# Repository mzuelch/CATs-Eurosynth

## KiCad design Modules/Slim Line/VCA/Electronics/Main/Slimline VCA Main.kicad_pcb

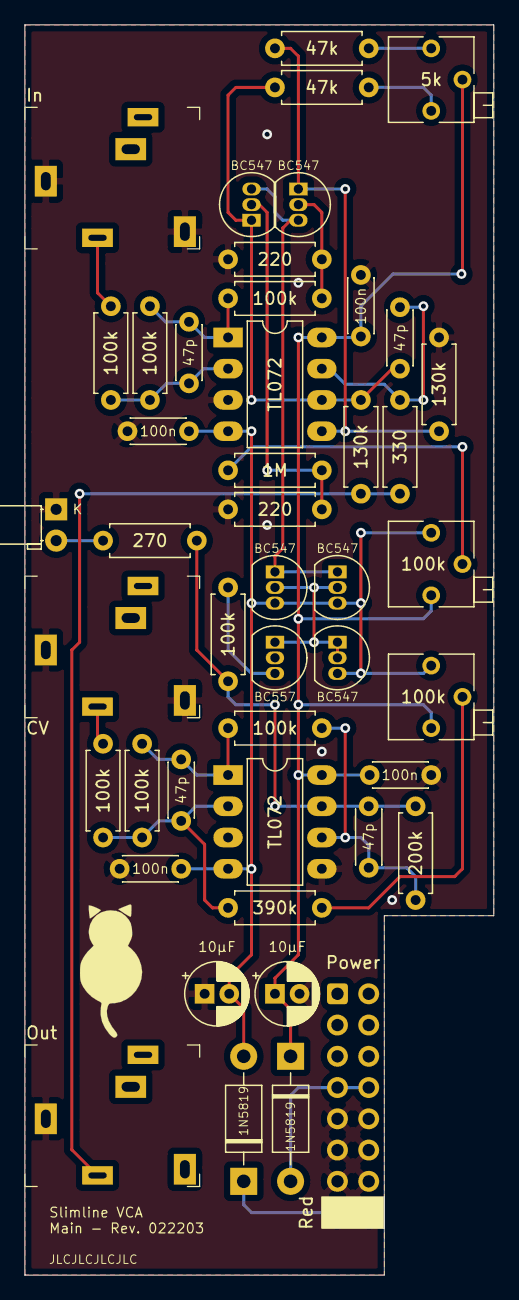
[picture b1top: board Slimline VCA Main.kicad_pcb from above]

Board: 2 copper layers, 38.1 x 101.6 mm, 46 parts (0 on the bottom side), 27 nets.

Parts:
C1, C2, C3, C4: 47p; C_Disc_D4.3mm_W1.9mm_P5.00mm
C5, C6: 10µF; CP_Radial_D5.0mm_P2.00mm
C7, C8, C9, C10: 100n; C_Disc_D4.3mm_W1.9mm_P5.00mm
D1, D2: 1N5819; D_DO-41_SOD81_P10.16mm_Horizontal
D3: LED; LED_D3.0mm_Horizontal_O1.27mm_Z2.0mm
J1: CV; Jack_3.5mm_QingPu_WQP-PJ324M
J2: In; Jack_3.5mm_QingPu_WQP-PJ324M
J3: Out; Jack_3.5mm_QingPu_WQP-PJ324M
J4: Power; Power_2x8_Horizontal
Q1: BC557; TO-92_Inline
Q2, Q3, Q4, Q5, Q6: BC547; TO-92_Inline
R1: 390k; R_Axial_DIN0207_L6.3mm_D2.5mm_P7.62mm_Horizontal
R2, R3, R4, R6, R7, R8, R9: 100k; R_Axial_DIN0207_L6.3mm_D2.5mm_P7.62mm_Horizontal
R5: 200k; R_Axial_DIN0207_L6.3mm_D2.5mm_P7.62mm_Horizontal
R10, R13: 220; R_Axial_DIN0207_L6.3mm_D2.5mm_P7.62mm_Horizontal
R11, R12: 47k; R_Axial_DIN0207_L6.3mm_D2.5mm_P7.62mm_Horizontal
R14: 1M; R_Axial_DIN0207_L6.3mm_D2.5mm_P7.62mm_Horizontal
R15, R16: 130k; R_Axial_DIN0207_L6.3mm_D2.5mm_P7.62mm_Horizontal
R17: 330; R_Axial_DIN0207_L6.3mm_D2.5mm_P7.62mm_Horizontal
R18: 270; R_Axial_DIN0207_L6.3mm_D2.5mm_P7.62mm_Horizontal
RV1, RV3: 100k; Potentiometer_Bourns_3266P_Horizontal
RV2: 5k; Potentiometer_Bourns_3266P_Horizontal
U1, U2: TL072; DIP-8_W7.62mm_LongPads

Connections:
+12V: C5.1, C7.2, C9.2, D1.1, RV1.1, RV2.2, RV3.1, U1.8, U2.8
-12V: C6.2, C8.1, C10.1, D2.2, Q2.3, Q4.3, Q5.3, RV1.3, RV3.3, U1.4, U2.4
GND: C5.2, C6.1, C7.1, C8.2, C9.1, C10.2, D3.1, J1.S, J1.TN, J2.S, J2.TN, J3.S, J4.GND, Q1.2, R10.2, R13.2, R15.2, U1.3, U2.3, U2.5
unnamed: C1.1, R3.1, R4.2, U2.1
unnamed: C1.2, R1.1, R2.1, R3.2, U2.2
unnamed: C2.1, R5.1, R6.2, R18.2, U2.7
unnamed: C2.2, R4.1, R5.2, U2.6
unnamed: C3.1, R8.1, R9.2, U1.1
unnamed: C3.2, R7.1, R8.2, U1.2
unnamed: C4.1, R17.2, U1.7
unnamed: C4.2, Q6.1, R12.2, R16.2, U1.6
unnamed: D1.2, J4.+12V
unnamed: D2.1, J4.-12V
unnamed: D3.2, R18.1
unnamed: J1.T, R2.2
unnamed: J2.T, R7.2
unnamed: J3.T, R16.1, R17.1
unnamed: Q1.1, Q2.1, Q2.2, Q4.2, Q5.2
unnamed: Q1.3, R6.1
unnamed: Q3.1, R11.2, R15.1, U1.5
unnamed: Q3.2, R9.1, R10.1
unnamed: Q3.3, Q4.1, Q5.1, Q6.3
unnamed: Q6.2, R13.1, R14.2
unnamed: R1.2, RV1.2
unnamed: R11.1, RV2.3
unnamed: R12.1, RV2.1
unnamed: R14.1, RV3.2

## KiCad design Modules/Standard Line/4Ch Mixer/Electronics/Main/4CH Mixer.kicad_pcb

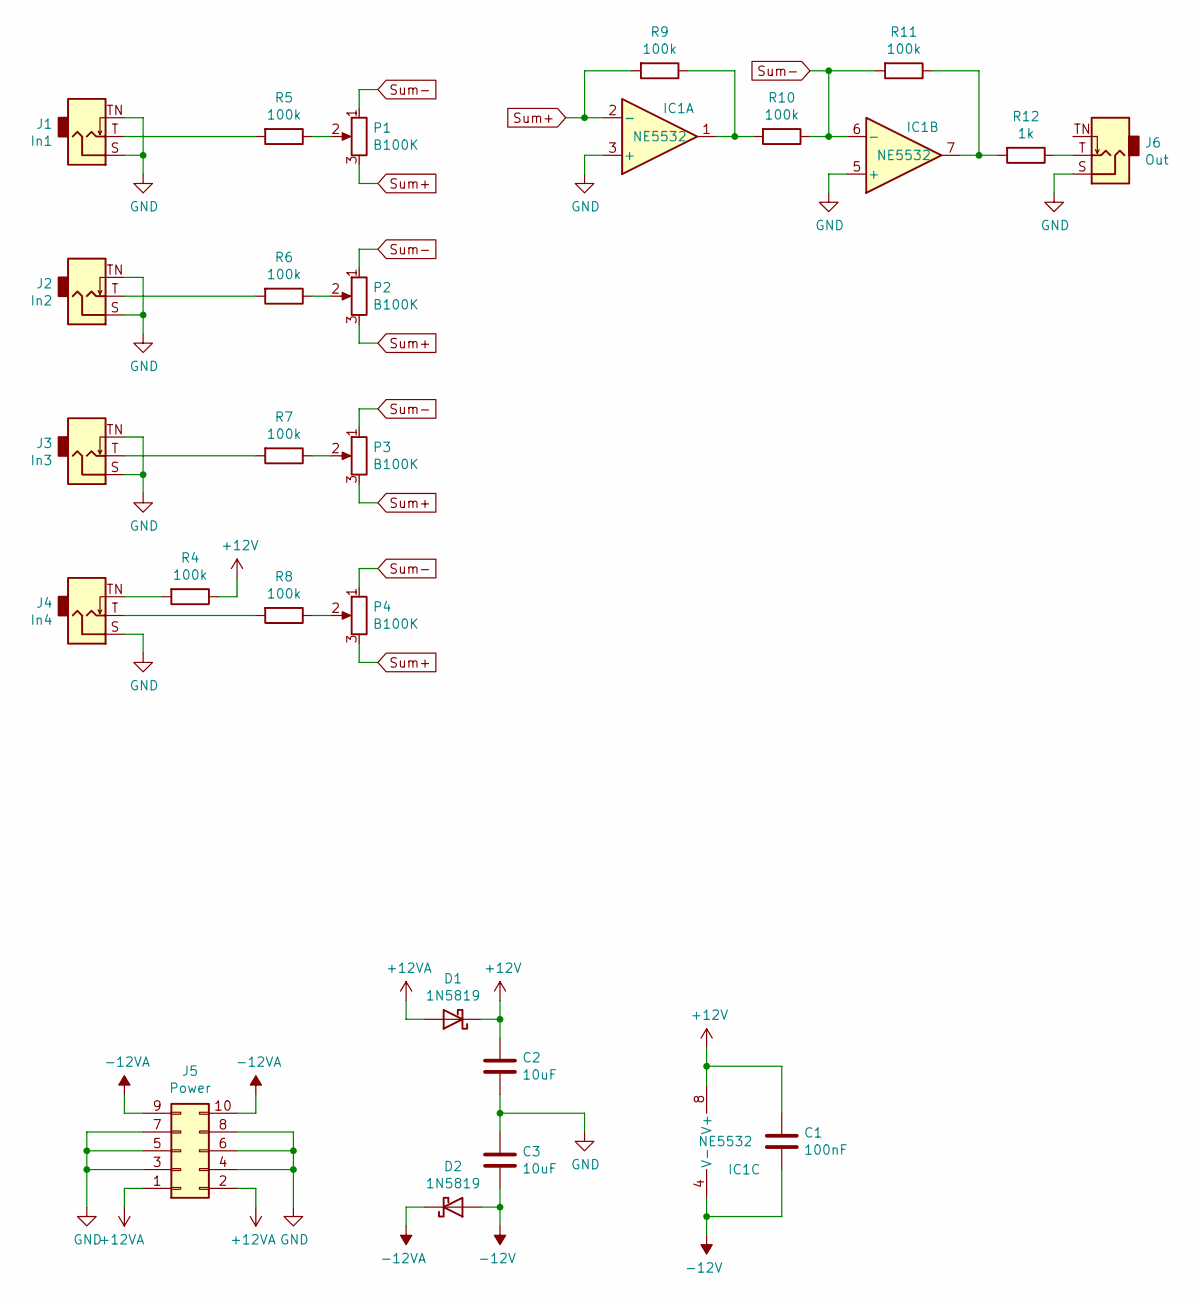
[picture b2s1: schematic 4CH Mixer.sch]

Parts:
C1: 100nF; C_0805_2012Metric; LCSC C49678
C2, C3: 10uF; C_0805_2012Metric; LCSC C15850
D1, D2: 1N5819; D_SOD-123; LCSC C8598
IC1: NE5532; SOIC-8_3.9x4.9mm_P1.27mm; LCSC C7426
J1: In1; PJ-301-M-12
J2: In2; PJ-301-M-12
J3: In3; PJ-301-M-12
J4: In4; PJ-301-M-12
J5: Power; PinHeader_2x05_P2.54mm_Vertical
J6: Out; PJ-301-M-12
P1, P2, P3, P4: B100K; Potentiometer_Alpha_RD901F-40-00D_Single_Vertical
R4, R5, R6, R7, R8, R9, R10, R11: 100k; R_0805_2012Metric; LCSC C17407
R12: 1k; R_0805_2012Metric; LCSC C17513

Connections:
+12V: C1.1, C2.1, D1.1 (K), IC1.8 (V+), R4.1
+12VA: D1.2 (A), J5.1, J5.2
-12V: C1.2, C3.2, D2.2 (A), IC1.4 (V-)
-12VA: D2.1 (K), J5.9, J5.10
GND: C2.2, C3.1, IC1.3 (+), IC1.5 (+), J1.S, J1.TN, J2.S, J2.TN, J3.S, J3.TN, J4.S, J5.3, J5.4, J5.5, J5.6, J5.7, J5.8, J6.S
unnamed: IC1.1, R9.1, R10.2
unnamed: IC1.7, R11.1, R12.2
unnamed: J1.T, R5.2
unnamed: J2.T, R6.2
unnamed: J3.T, R7.2
unnamed: J4.T, R8.2
unnamed: J4.TN, R4.2
unnamed: J6.T, R12.1
unnamed: P1.2, R5.1
unnamed: P2.2, R6.1
unnamed: P3.2, R7.1
unnamed: P4.2, R8.1
Sum+: IC1.2 (-), P1.3, P2.3, P3.3, P4.3, R9.2
Sum-: IC1.6 (-), P1.1, P2.1, P3.1, P4.1, R10.1, R11.2

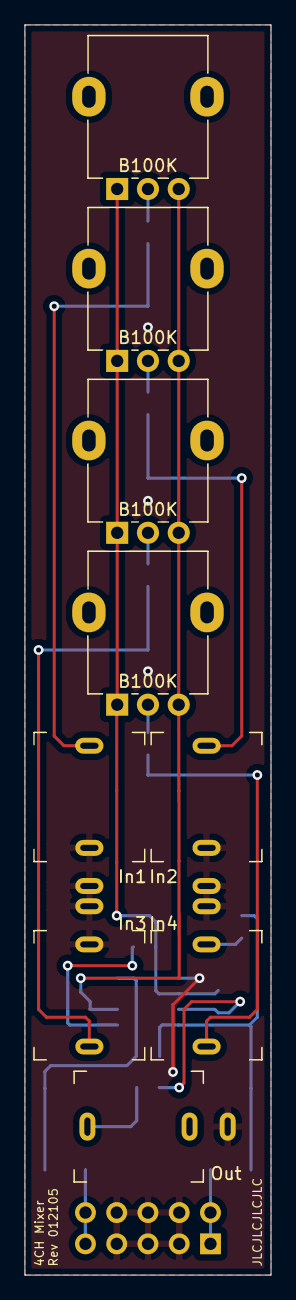
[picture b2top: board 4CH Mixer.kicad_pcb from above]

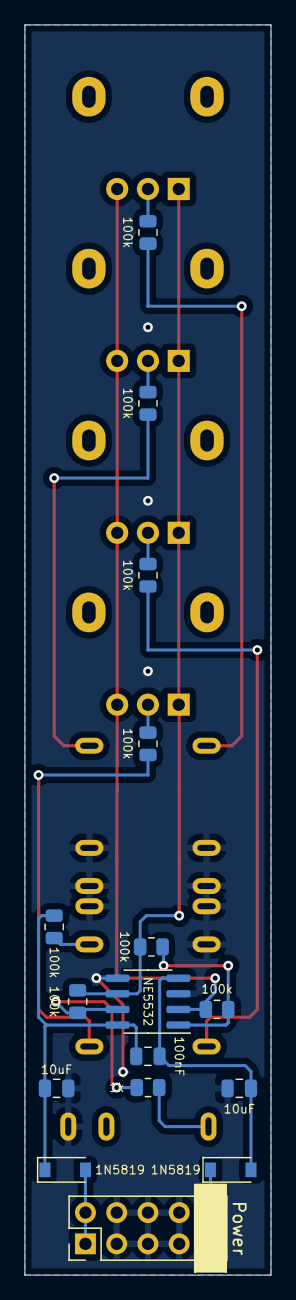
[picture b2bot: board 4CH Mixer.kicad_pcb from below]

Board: 2 copper layers, 20.0 x 101.6 mm, 25 parts (16 on the bottom side), 19 nets.

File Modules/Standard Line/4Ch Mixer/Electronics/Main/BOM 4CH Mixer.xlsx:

Comment | Designator | Footprint | LCSC
1N5819 | D2,D1 | D_SOD-123 | C8598
10uF | C3,C2 | C_0805_2012Metric | C15850
Out | J6 | PJ-301-M-12
In4 | J4 | PJ-301-M-12
In3 | J3 | PJ-301-M-12
In2 | J2 | PJ-301-M-12
In1 | J1 | PJ-301-M-12
NE5532 | IC1 | SOIC-8_3.9x4.9mm_P1.27mm | C7426
1k | R12 | R_0805_2012Metric | C17513
100k | R11,R10,R9,R8,R7,R6,R5,R4 | R_0805_2012Metric | C17407
B100K | P4,P3,P2,P1 | Potentiometer_Alpha_RD901F-40-00D_Single_Vertical
Power | J5 | PinHeader_2x05_P2.54mm_Vertical
100nF | C1 | C_0805_2012Metric | C49678

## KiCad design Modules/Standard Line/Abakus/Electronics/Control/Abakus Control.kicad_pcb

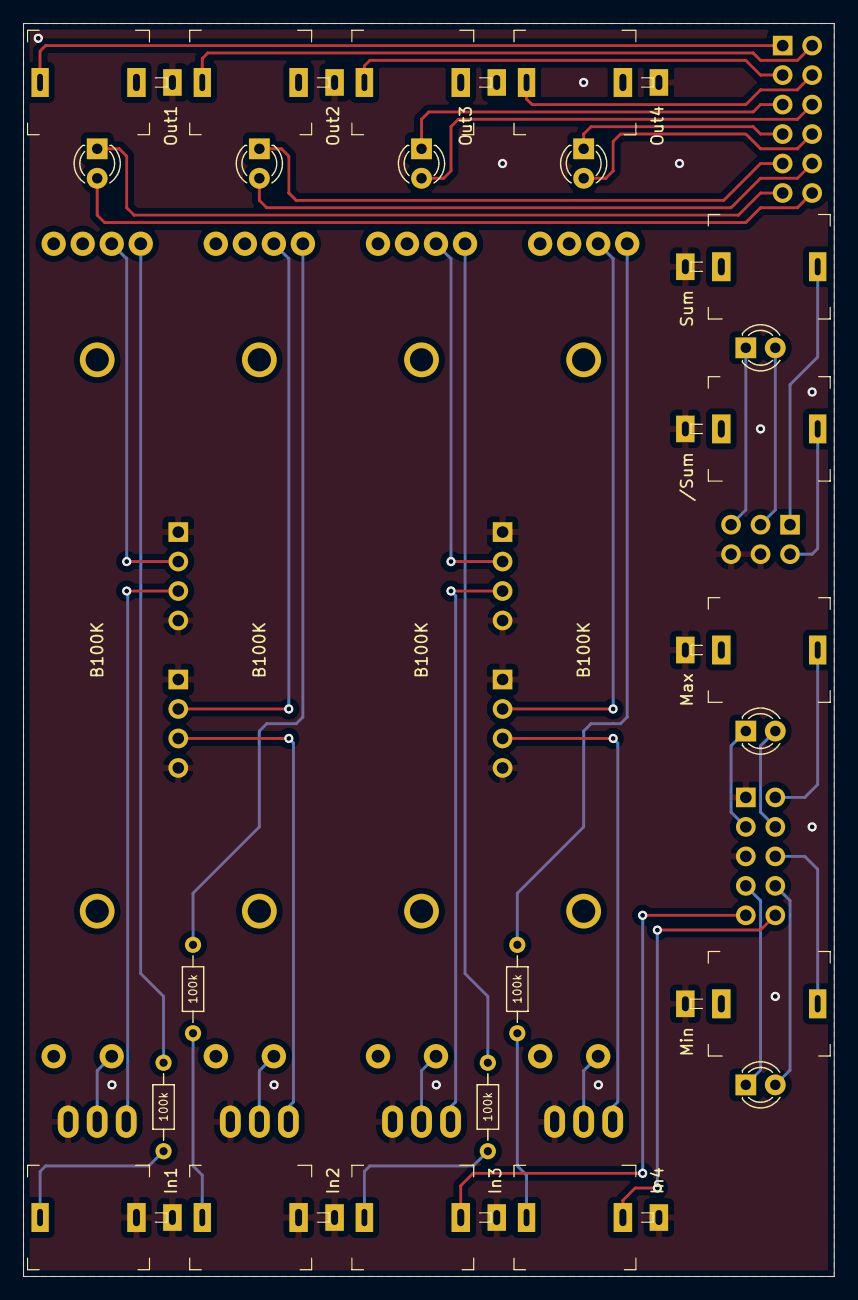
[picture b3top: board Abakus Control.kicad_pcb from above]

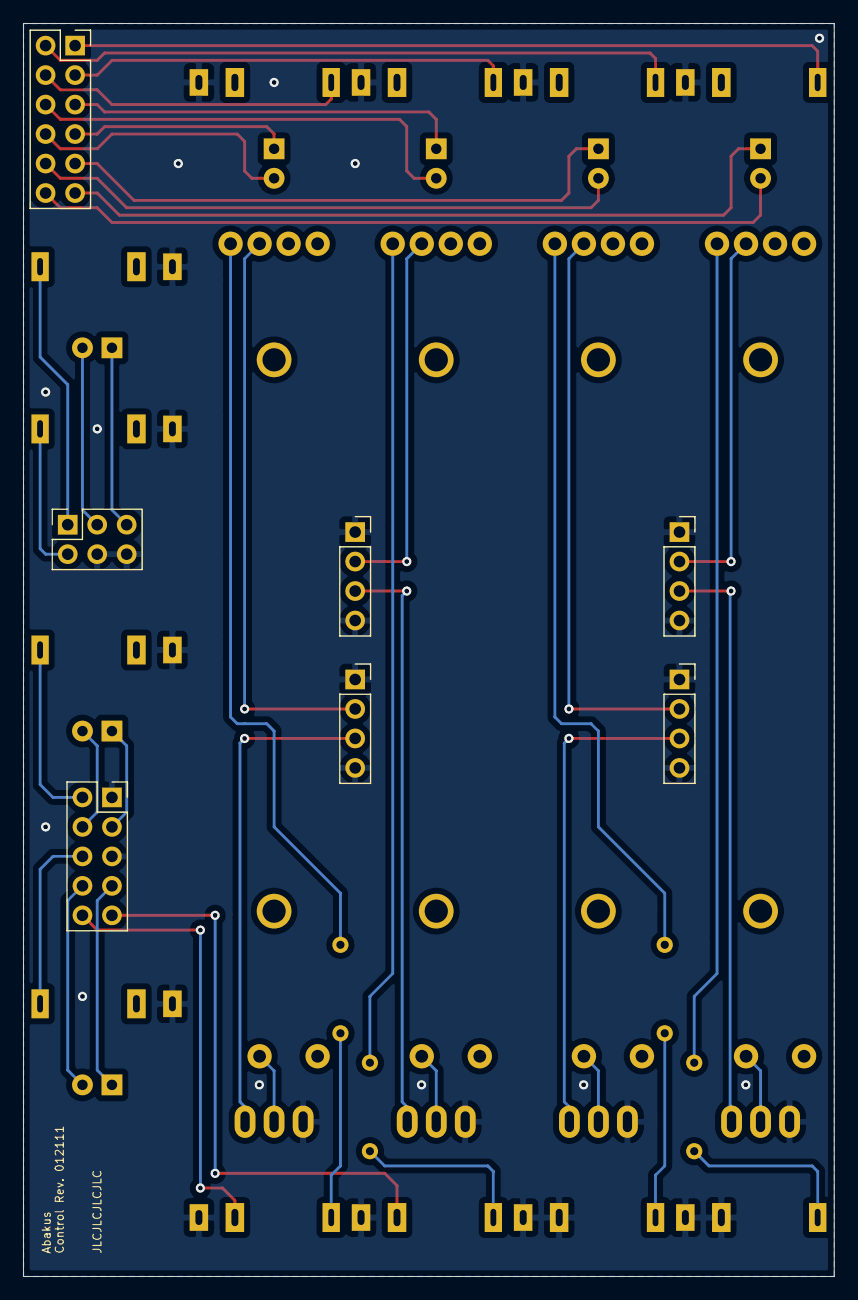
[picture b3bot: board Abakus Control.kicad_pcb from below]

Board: 2 copper layers, 69.8 x 108.0 mm, 38 parts (7 on the bottom side), 45 nets.

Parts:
D1: Out1; LED_D3.0mm
D2: Out2; LED_D3.0mm
D3: Out3; LED_D3.0mm
D4: Out4; LED_D3.0mm
D5: Min; LED_D3.0mm
D6: Sum; LED_D3.0mm
D7: Max; LED_D3.0mm
J1: In1; Jack_3.5mm_QingPu_WQP-PJ301M-12
J2: In2; Jack_3.5mm_QingPu_WQP-PJ301M-12
J3: In3; Jack_3.5mm_QingPu_WQP-PJ301M-12
J4: In4; Jack_3.5mm_QingPu_WQP-PJ301M-12
J5: Out1; Jack_3.5mm_QingPu_WQP-PJ301M-12
J6: Out2; Jack_3.5mm_QingPu_WQP-PJ301M-12
J7: Out3; Jack_3.5mm_QingPu_WQP-PJ301M-12
J8: Out4; Jack_3.5mm_QingPu_WQP-PJ301M-12
J9: /Sum; Jack_3.5mm_QingPu_WQP-PJ301M-12
J10: Sum; Jack_3.5mm_QingPu_WQP-PJ301M-12
J11: Max; Jack_3.5mm_QingPu_WQP-PJ301M-12
J12: Min; Jack_3.5mm_QingPu_WQP-PJ301M-12
J13: Out; PinSocket_2x06_P2.54mm_Vertical
J14: In1; PinSocket_1x04_P2.54mm_Vertical
J15: In2; PinSocket_1x04_P2.54mm_Vertical
J16: In3; PinSocket_1x04_P2.54mm_Vertical
J17: In4; PinSocket_1x04_P2.54mm_Vertical
J18: Sum; PinSocket_2x03_P2.54mm_Vertical
J19: MinMax; PinSocket_2x05_P2.54mm_Vertical
P1, P2, P3, P4: B100K; Potentiometer_AlpsAlpine_RS6011YA9A07
R1, R2, R3, R4: 100k; R_Axial_DIN0204_L3.6mm_D1.6mm_P7.62mm_Horizontal
SW1: Att/AV1; SMTS-102-2xxx
SW2: Att/AV2; SMTS-102-2xxx
SW3: Att/AV3; SMTS-102-2xxx
SW4: Att/AV4; SMTS-102-2xxx

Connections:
+5V: J3.TN, J19.9
+10V: J4.TN, J19.10
+In1: J14.2, P1.CW
+In2: J15.2, P2.CW
+In3: J16.2, P3.CW
+In4: J17.2, P4.CW
-In1: J14.3, SW1.1
-In2: J15.3, SW2.1
-In3: J16.3, SW3.1
-In4: J17.3, SW4.1
GND: J1.S, J1.TN, J2.S, J2.TN, J3.S, J4.S, J5.S, J6.S, J7.S, J8.S, J9.S, J10.S, J11.S, J12.S, J14.1, J14.4, J15.1, J15.4, J16.1, J16.4, J17.1, J17.4, J18.4, J18.6, J19.1, J19.5, SW1.3, SW2.3, SW3.3, SW4.3
Inv_Sum: J9.T, J18.2
LED_Max_1: D7.1, J19.3
LED_Max_2: D7.2, J19.4
LED_Min_1: D5.1, J19.7
LED_Min_2: D5.2, J19.8
LED_Out_1_1: D1.1, J13.11
LED_Out_1_2: D1.2, J13.12
LED_Out_2_1: D2.1, J13.9
LED_Out_2_2: D2.2, J13.10
LED_Out_3_1: D3.1, J13.5
LED_Out_3_2: D3.2, J13.6
LED_Out_4_1: D4.1, J13.7
LED_Out_4_2: D4.2, J13.8
LED_Sum_1: D6.1, J18.5
LED_Sum_2: D6.2, J18.3
Max: J11.T, J19.2
Min: J12.T, J19.6
unnamed: J1.T, R1.2
unnamed: J2.T, R2.2
unnamed: J3.T, R3.2
unnamed: J4.T, R4.2
unnamed: P1.CCW, SW1.2
unnamed: P1.W, R1.1
unnamed: P2.CCW, SW2.2
unnamed: P2.W, R2.1
unnamed: P3.CCW, SW3.2
unnamed: P3.W, R3.1
unnamed: P4.CCW, SW4.2
unnamed: P4.W, R4.1
Out1: J5.T, J13.1
Out2: J6.T, J13.2
Out3: J7.T, J13.3
Out4: J8.T, J13.4
Sum: J10.T, J18.1

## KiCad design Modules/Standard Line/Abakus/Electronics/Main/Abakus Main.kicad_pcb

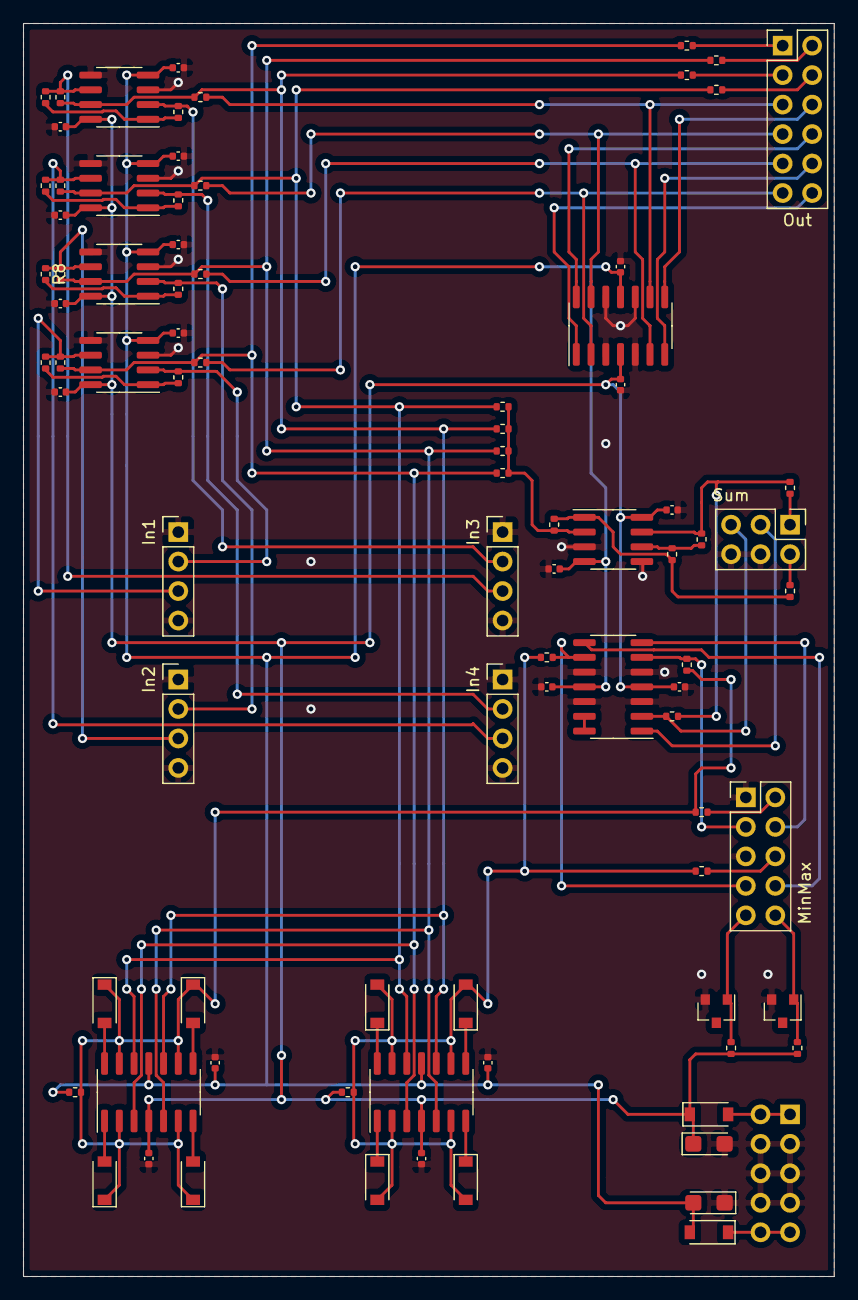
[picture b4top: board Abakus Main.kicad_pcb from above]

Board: 2 copper layers, 69.8 x 108.0 mm, 87 parts (1 on the bottom side), 60 nets.

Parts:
C1, C2: 10µ; CP_EIA-3216-18_Kemet-A
C3, C4, C5, C6, C7, C8, C9, C10, C11, C12, C13, C14, C15, C16, C17, C18, C19, C20: 100n; C_0402_1005Metric
D1, D2: B5817W; D_SOD-123
D3, D4, D5, D6, D7, D8, D9, D10: 1N4148W; D_SOD-123
J1: Power; Power_2x5_Vertical
J2: Out; PinHeader_2x06_P2.54mm_Vertical
J3: In1; PinHeader_1x04_P2.54mm_Vertical
J4: In2; PinHeader_1x04_P2.54mm_Vertical
J5: In3; PinHeader_1x04_P2.54mm_Vertical
J6: In4; PinHeader_1x04_P2.54mm_Vertical
J7: Sum; PinHeader_2x03_P2.54mm_Vertical
J8: MinMax; PinHeader_2x05_P2.54mm_Vertical
R1, R2, R3, R4, R7, R8, R9, R10, R11, R12, R13, R14, R21, R22, R23, R24, R27, R29, R30: 100k; R_0402_1005Metric
R5, R6, R15, R16, R17, R18, R19, R20, R25, R26, R28, R31, R32, R34, R36, R37, R38: 1k; R_0402_1005Metric
R33, R35: 10k; R_0402_1005Metric
U1, U2, U3, U4, U5: TL072CDT; SOIC-8_3.9x4.9mm_P1.27mm
U6, U7, U8, U9: TL074CDR; SOIC-14_3.9x8.7mm_P1.27mm
U10: LM4040AIM3-5.0/NOPB; SOT-23
U11: LM4040C10IDBZR; SOT-23

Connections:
+5V: J8.9, R37.1, U10.1
+10V: J8.10, R38.1, U11.1
+12V: C1.1, C3.1, C5.1, C7.1, C9.1, C11.1, C13.1, C15.1, C17.1, C19.1, D1.1, R35.2, R37.2, R38.2, U1.8, U2.8, U3.8, U4.8, U5.8, U6.4, U7.4, U8.4, U9.4
+In1: J3.2, R1.2, U1.2
+In2: J4.2, R2.2, U2.2
+In3: J5.2, R3.2, U3.2
+In4: J6.2, R4.2, U4.2
-12V: C2.2, C4.2, C6.2, C8.2, C10.2, C12.2, C14.2, C16.2, C18.2, C20.2, D2.2, R33.1, U1.4, U2.4, U3.4, U4.4, U5.4, U6.11, U7.11, U8.11, U9.11
-In1: J3.3, R7.1, R11.2, U1.6
-In2: J4.3, R8.1, R12.2, U2.6
-In3: J5.3, R9.1, R13.2, U3.6
-In4: J6.3, R10.1, R14.2, U4.6
GND: C1.2, C2.1, C3.2, C4.1, C5.2, C6.1, C7.2, C8.1, C9.2, C10.1, C11.2, C12.1, C13.2, C14.1, C15.2, C16.1, C17.2, C18.1, C19.2, C20.1, J1.GND, J3.1, J3.4, J4.1, J4.4, J5.1, J5.4, J6.1, J6.4, J7.4, J7.6, J8.1, J8.5, U1.3, U1.5, U2.3, U2.5, U3.3, U3.5, U4.3, U4.5, U5.3, U5.5, U8.3, U8.5, U8.10, U8.12, U9.3, U9.5, U9.10, U9.12, U10.2, U11.2
Int_Inv_Sum: R27.1, R28.2, R29.2, U5.1
Int_Max: D3.1, D4.1, D5.1, D6.1, R31.2, R33.2, R34.2, U6.2, U6.6, U6.9, U6.13
Int_Min: D7.2, D8.2, D9.2, D10.2, R26.2, R35.1, R36.2, U7.2, U7.6, U7.9, U7.13
Int_Out1: R5.2, R11.1, R17.2, R21.2, U1.7, U6.3, U7.3
Int_Out2: R12.1, R15.2, R18.2, R22.2, U2.7, U6.5, U7.5
Int_Out3: R6.2, R13.1, R19.2, R23.2, U3.7, U6.10, U7.10
Int_Out4: R14.1, R16.2, R20.2, R24.2, U4.7, U6.12, U7.12
Int_Sum: R25.2, R30.1, R32.2, U5.7
Inv_Sum: J7.2, R28.1
LED_Max_1: J8.3, R31.1, U9.6
LED_Max_2: J8.4, U9.7
LED_Min_1: J8.7, R26.1, U9.9
LED_Min_2: J8.8, U9.8
LED_Out_1_1: J2.11, R5.1, U8.2
LED_Out_1_2: J2.12, U8.1
LED_Out_2_1: J2.9, R15.1, U8.6
LED_Out_2_2: J2.10, U8.7
LED_Out_3_1: J2.5, R6.1, U8.9
LED_Out_3_2: J2.6, U8.8
LED_Out_4_1: J2.7, R16.1, U8.13
LED_Out_4_2: J2.8, U8.14
LED_Sum_1: J7.5, R25.1, U9.2
LED_Sum_2: J7.3, U9.1
Max: J8.2, R34.1
Min: J8.6, R36.1
unnamed: D1.2, J1.+12V
unnamed: D2.1, J1.-12V
unnamed: D3.2, U6.1
unnamed: D4.2, U6.7
unnamed: D5.2, U6.8
unnamed: D6.2, U6.14
unnamed: D7.1, U7.1
unnamed: D8.1, U7.7
unnamed: D9.1, U7.8
unnamed: D10.1, U7.14
unnamed: R1.1, R7.2, U1.1
unnamed: R2.1, R8.2, U2.1
unnamed: R3.1, R9.2, U3.1
unnamed: R4.1, R10.2, U4.1
unnamed: R21.1, R22.1, R23.1, R24.1, R27.2, U5.2
unnamed: R29.1, R30.2, U5.6
unnamed: U9.13, U9.14
Out1: J2.1, R17.1
Out2: J2.2, R18.1
Out3: J2.3, R19.1
Out4: J2.4, R20.1
Sum: J7.1, R32.1
